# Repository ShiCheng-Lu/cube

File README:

# Display Cube

You seen those anamorphic billboards that looks 3D from a certain perspective? Now it's a desktop cube, and it looks 3D from every perspective.

### Full stack!

The goal of the project is to build a cube that has three sides with displays, and one camera to track where your eye is. The displays can show images in just the right way depending on where your eye is to make something appear 3D.

### Hardware

The Raspberry Pi 5 only has 2 HDMI (micro) output ports, in order to drive all 3 displays, we need to leverage one of the two the MIPI outputs from the rpi. HOWEVER! the rpi uses a 22 pin MIPI output where as the display (and almost all DIY displays out there) uses 30 pins and requires some sort of LED driver to power the LED pins in the 30 pin input. The `mipi-adapter` directory contains the KiCad design to convert the 22 pin MIPI data output, along with a USB-C for power input into the 30 pin required for the display.

The hardware design accounts for impedance matching (100 ohm for the MIPI standard), which probably does not matter at all due to the frequency I'm running the MIPI data lines at to power my 720x720 output resolution. The USB-C plug is in fact properly connected with 2 5.1k resistors down to ground so it will work with any USB-C charger (unlike the initial batch of Raspberry Pi 4).

Another problem is that I have 3 displays and 1 Raspberry Pi to power, to accomodate this, I have designed a USB-C power splitter in `usb-power`. This board takes one USB-C input, connects up the VCC, GND, and the two CC power delivery negotiation pins into the Raspberry Pi so it can negotiate 5V 5A from the "Official Raspberry Pi Power Supply Unit". Unbeknownst to the Raspberry Pi and the power supply, there are 4 (for symmetry, I only need 3) USB plugs syphoning a couple amp on top of what the raspberry pi will use. This should be safe as long as my displays don't draw more than 2A total.

### Firmware

Initially I had high hopes that the display driver won't be an issue due to the display advertising the JD9365 driver, which has compatible drivers in the linux kernel. My disappointment quickly became inmeasurable and my day ruined, as I realized the displays are using the JD9365TX driver chip, which are totally incompatible with the JD9365D driver code. Luckly for me, the display supplier has provided me with all the resources the write a kernal driver for this display. With the help of my good friend Claude, there should be a working KMS display driver under the `mipi-driver` directory.

### Software

Rendering in C++ and vulkan

### Harderware

The box: using FreeCAD

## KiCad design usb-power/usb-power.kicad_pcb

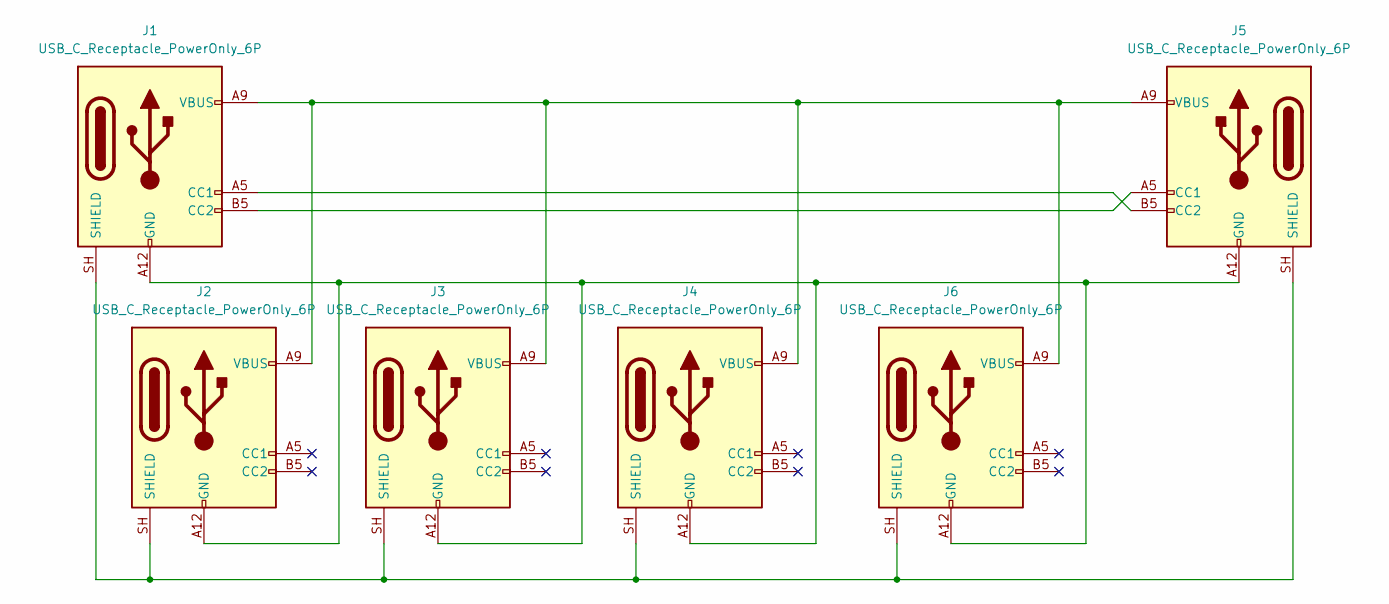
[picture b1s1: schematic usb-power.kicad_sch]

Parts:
J1, J2, J3, J4, J5, J6: USB_C_Receptacle_PowerOnly_6P; USB_C_Receptacle_GCT_USB4125-xx-x_6P_TopMnt_Horizontal

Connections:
unnamed: J1.A5 (CC1), J5.B5 (CC2)
unnamed: J1.B5 (CC2), J5.A5 (CC1)
unnamed: J1.A12 (GND), J1.B12 (GND), J2.A12 (GND), J2.B12 (GND), J3.A12 (GND), J3.B12 (GND), J4.A12 (GND), J4.B12 (GND), J5.A12 (GND), J5.B12 (GND), J6.A12 (GND), J6.B12 (GND)
unnamed: J1.SH (SHIELD), J2.SH (SHIELD), J3.SH (SHIELD), J4.SH (SHIELD), J5.SH (SHIELD), J6.SH (SHIELD)
unnamed: J1.A9 (VBUS), J1.B9 (VBUS), J2.A9 (VBUS), J2.B9 (VBUS), J3.A9 (VBUS), J3.B9 (VBUS), J4.A9 (VBUS), J4.B9 (VBUS), J5.A9 (VBUS), J5.B9 (VBUS), J6.A9 (VBUS), J6.B9 (VBUS)

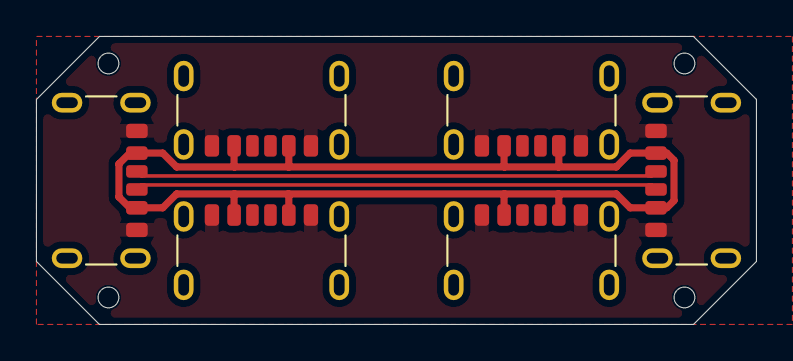
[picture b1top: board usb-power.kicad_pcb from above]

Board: 2 copper layers, 40.0 x 16.0 mm, 6 parts (0 on the bottom side), 5 nets.

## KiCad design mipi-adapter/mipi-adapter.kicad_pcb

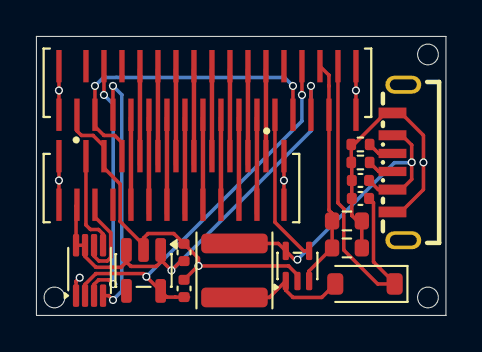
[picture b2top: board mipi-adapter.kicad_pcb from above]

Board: 4 copper layers, 22.8 x 15.5 mm, 16 parts (0 on the bottom side), 32 nets.

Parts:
C1, C2, C3, C4: 1uF; C_0402_1005Metric
D1: D_Schottky; D_SOD-123
J1: Connector; HRS_TF38-22S-0.5SV_830_
J4: Conn_01x30_Socket; HRS_TF38-30S-0.5SV_830_
J5: USB_C_Receptacle_PowerOnly_6P; USB-C-SMD_TYPE-C--015
L1: 10uH; L_APV_ANR4012
R1, R2: 5.1; R_0603_1608Metric
R3, R4: 5.1k; R_0402_1005Metric
U1: TPS61169; SOT-353_SC-70-5
U2: PCA9306; VSSOP-8_2.3x2mm_P0.5mm
U3: TPS7A2018; SOT-23-5

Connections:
unnamed: D1.2 (A), L1.1, U1.1 (SW)
unnamed: C4.1, D1.1 (K), J4.30
unnamed: J1.9 (CLKN), J4.14
unnamed: J1.8 (CLKP), J4.15
unnamed: J1.3 (D0N), J4.20
unnamed: J1.2 (D0P), J4.21
unnamed: J1.6 (D1N), J4.17
unnamed: J1.5 (D1P), J4.18
unnamed: J1.12 (D2N), J4.11
unnamed: J1.11 (D2P), J4.12
unnamed: J1.15 (D3N), J4.8
unnamed: J1.14 (D3P), J4.9
unnamed: J1.17 (PWR_EN), J4.3, J4.25
unnamed: J1.20 (SCL), U2.6 (SCL2)
unnamed: J1.21 (SDA), U2.5 (SDA2)
unnamed: J1.SH (SHIELD), J4.SH (SHIELD), J5.SH (SHIELD)
unnamed: C1.2, J1.22 (VCC), J4.27, U2.7 (VREF2), U2.8 (EN), U3.1 (IN), U3.3 (EN)
unnamed: C1.1, C2.1, C3.2, C4.2, J1.19 (GND), J4.1, J5.A12 (GND), J5.B12 (GND), R1.2, R2.2, R3.1, R4.1, U1.2 (GND), U2.1 (GND), U3.2 (GND)
unnamed: J4.4, U2.3 (SCL1)
unnamed: J4.5, U2.4 (SDA1)
unnamed: J1.16 (GND), J4.7
unnamed: J1.13 (GND), J4.10
unnamed: J1.10 (GND), J4.13
unnamed: J1.7 (GND), J4.16
unnamed: J1.4 (GND), J4.19
unnamed: J1.1 (GND), J4.22
unnamed: J4.23, U1.4 (EN)
unnamed: C2.2, J4.26, U2.2 (VREF1), U3.5 (OUT)
unnamed: J4.28, J4.29, R1.1, R2.1, U1.3 (FB)
unnamed: J5.A5 (CC1), R3.2
unnamed: J5.B5 (CC2), R4.2
unnamed: C3.1, J5.A9 (VBUS), J5.B9 (VBUS), L1.2, U1.5 (VIN)
